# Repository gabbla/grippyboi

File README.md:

# GrippyBoi

Open source and open hardware Haldex gen 1 controller.

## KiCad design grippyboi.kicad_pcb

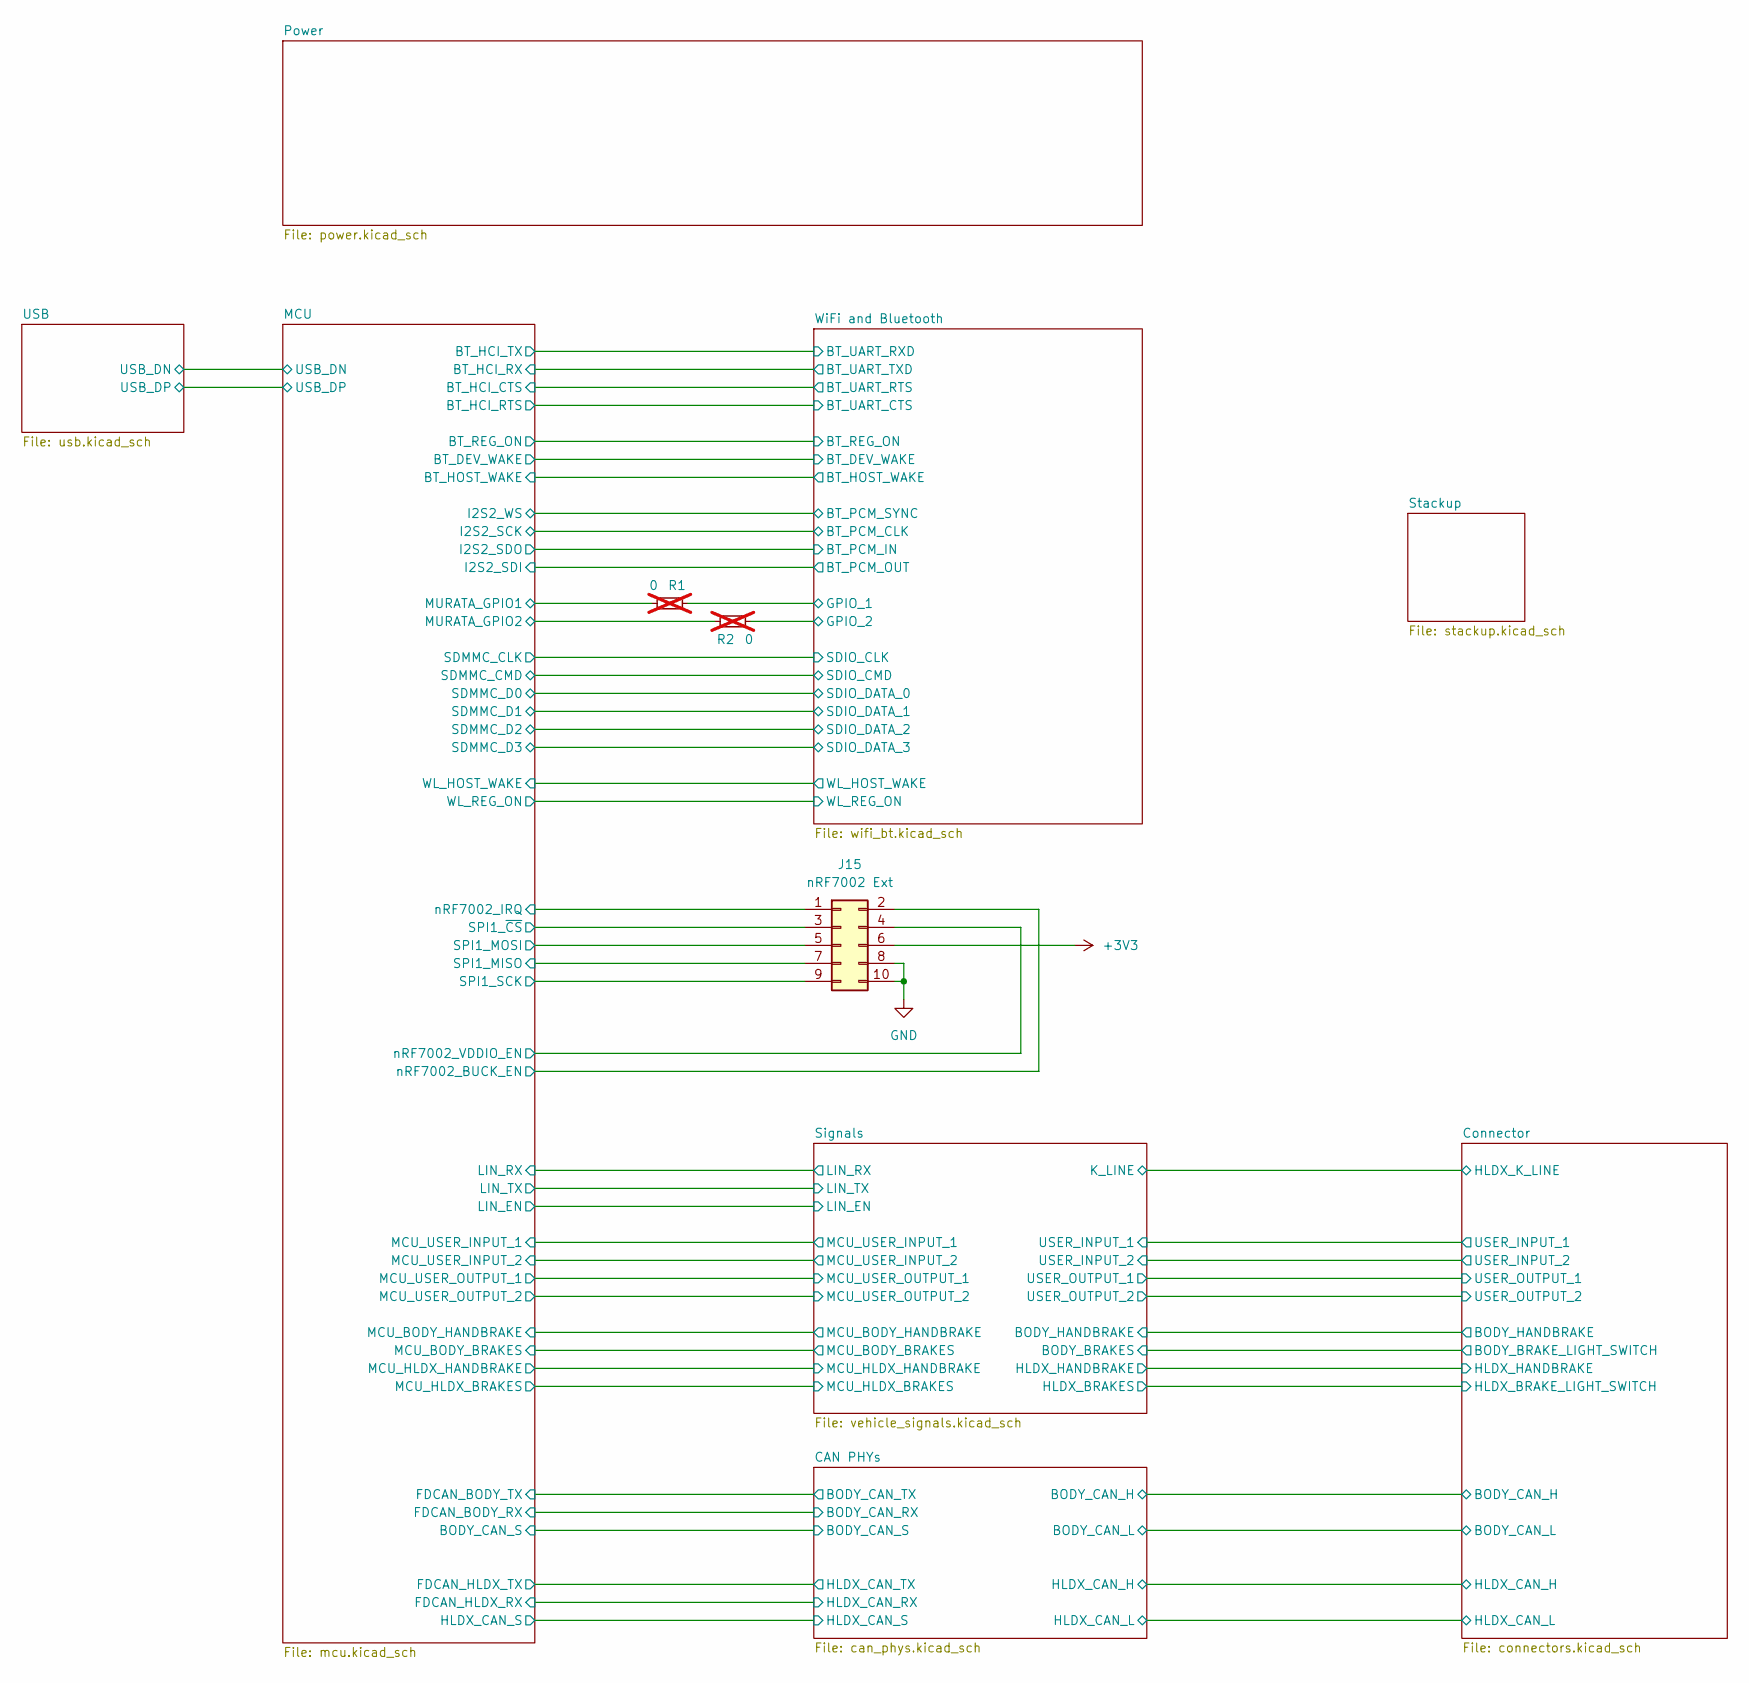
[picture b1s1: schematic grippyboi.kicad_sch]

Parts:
J15: nRF7002 Ext; PinHeader_2x05_P1.27mm_Vertical
R1, R2: 0; R_0603_1608Metric_Pad0.98x0.95mm_HandSolder; not fitted

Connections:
+3V3: J15.6; also elsewhere on the board
/MCU/MURATA_GPIO1: R1.2; also elsewhere on the board
/MCU/MURATA_GPIO2: R2.1; also elsewhere on the board
/MCU/SPI1_MISO: J15.7; also elsewhere on the board
/MCU/SPI1_MOSI: J15.5; also elsewhere on the board
/MCU/SPI1_SCK: J15.9; also elsewhere on the board
/MCU/SPI1_~CS: J15.3; also elsewhere on the board
/MCU/nRF7002_BUCK_EN: J15.2; also elsewhere on the board
/MCU/nRF7002_IRQ: J15.1; also elsewhere on the board
/MCU/nRF7002_VDDIO_EN: J15.4; also elsewhere on the board
/WiFi and Bluetooth/GPIO_1: R1.1; also elsewhere on the board
/WiFi and Bluetooth/GPIO_2: R2.2; also elsewhere on the board
GND: J15.8, J15.10; also elsewhere on the board

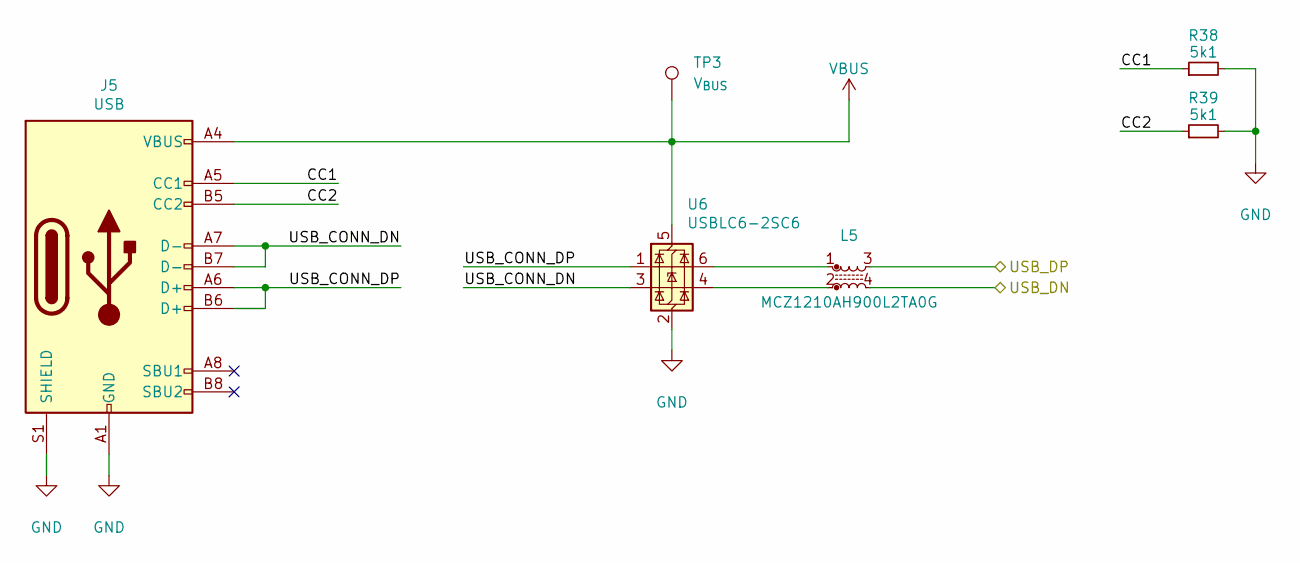
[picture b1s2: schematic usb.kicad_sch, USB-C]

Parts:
J5: USB; USB_C_Receptacle_G-Switch_GT-USB-7010ASV
L5: MCZ1210AH900L2TA0G; MCZ1210AH201L2TA0G
R38, R39: 5k1; R_0603_1608Metric_Pad0.98x0.95mm_HandSolder
TP3: V_{BUS}; TestPoint_Pad_D1.0mm
U6: USBLC6-2SC6; SOT-23-6

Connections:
/MCU/USB_DN: L5.4; also elsewhere on the board
/MCU/USB_DP: L5.3; also elsewhere on the board
/USB/CC1: J5.A5 (CC1), R38.1
/USB/CC2: J5.B5 (CC2), R39.1
/USB/USB_CONN_DN: J5.A7 (D-), J5.B7 (D-), U6.3 (I/O2)
/USB/USB_CONN_DP: J5.A6 (D+), J5.B6 (D+), U6.1 (I/O1)
GND: J5.A1 (GND), J5.A12 (GND), J5.B1 (GND), J5.B12 (GND), J5.S1 (SHIELD), R38.2, R39.2, U6.2 (GND); also elsewhere on the board
unnamed: L5.1, U6.6 (I/O1)
unnamed: L5.2, U6.4 (I/O2)
VBUS: J5.A4 (VBUS), J5.A9 (VBUS), J5.B4 (VBUS), J5.B9 (VBUS), TP3.1, U6.5 (VBUS)

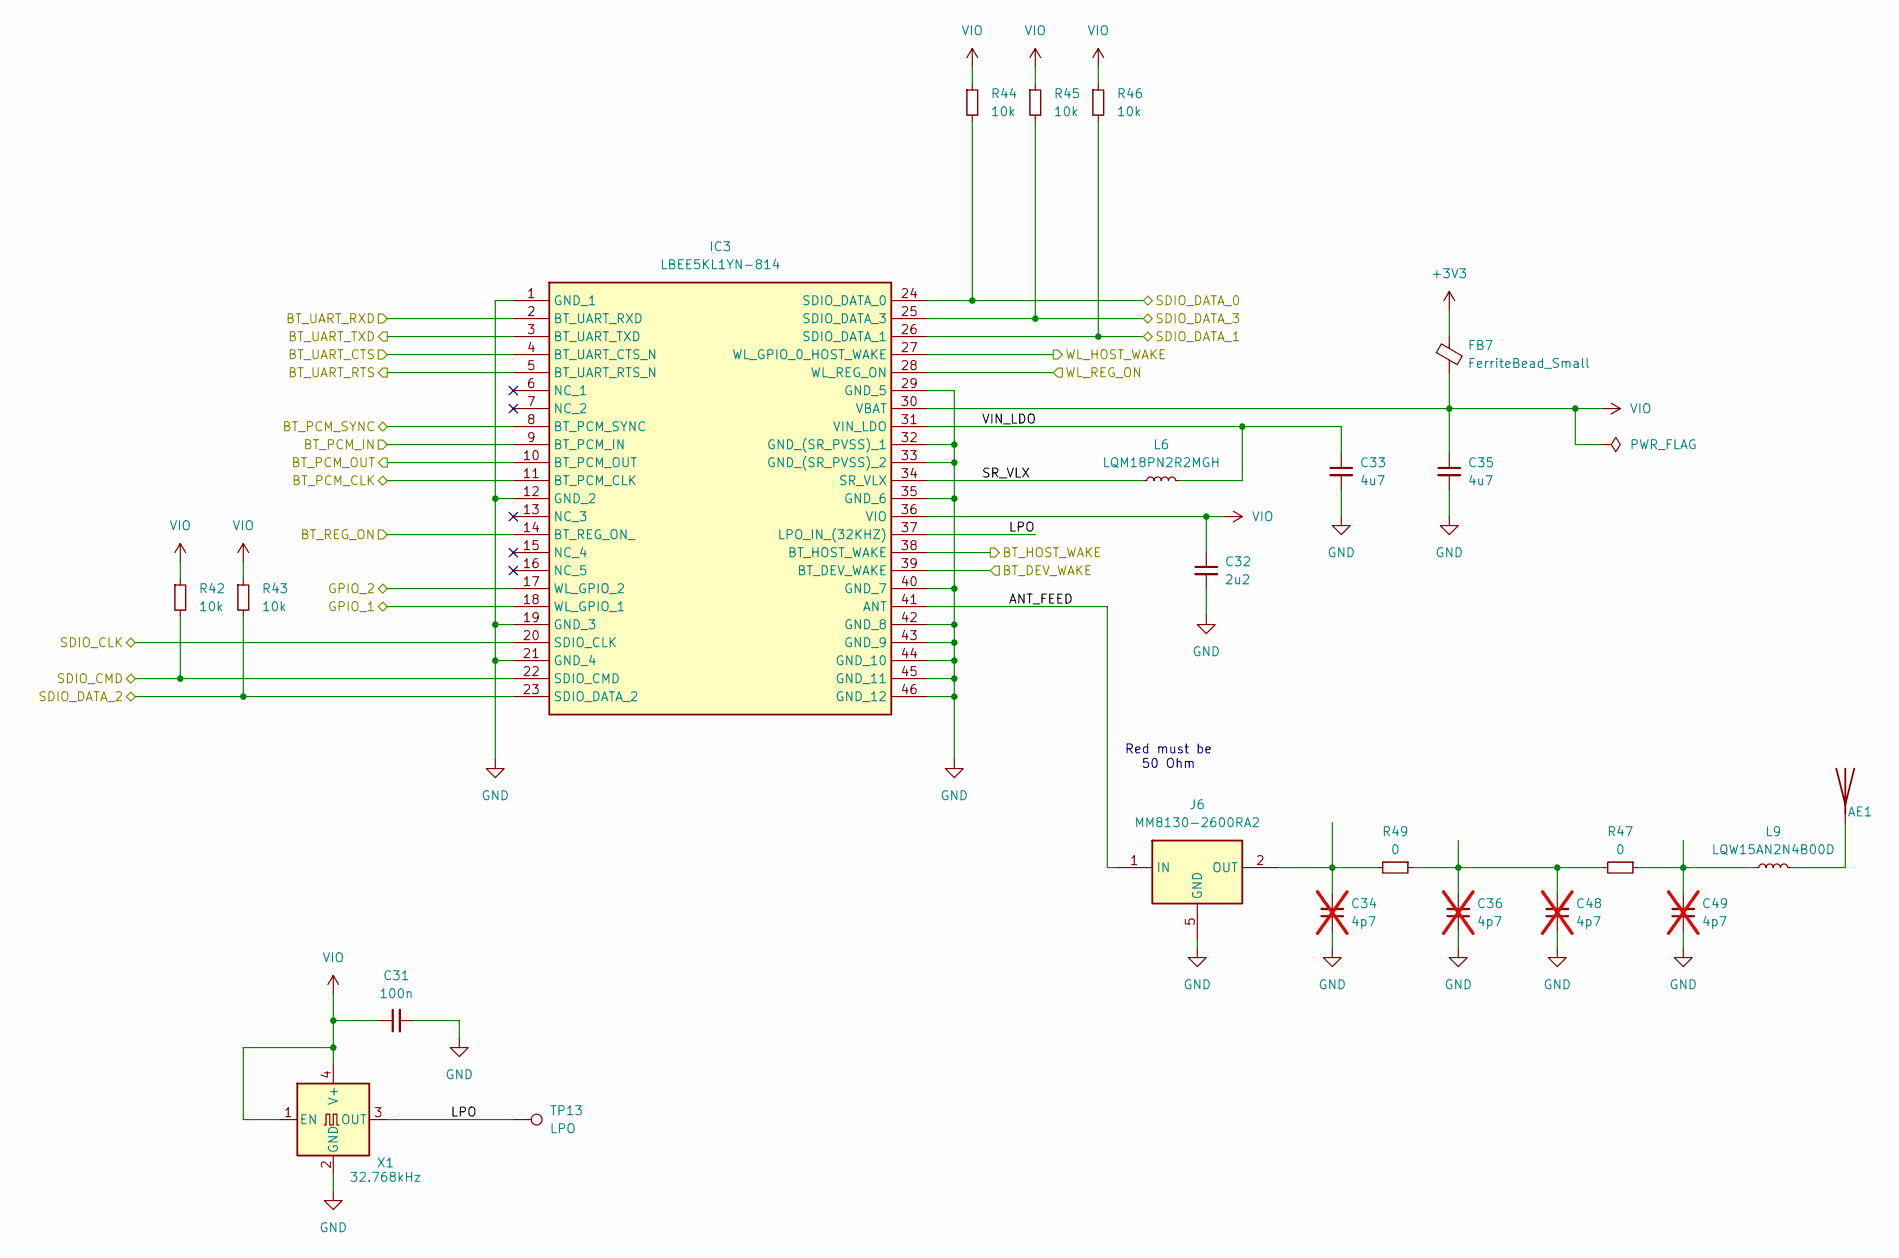
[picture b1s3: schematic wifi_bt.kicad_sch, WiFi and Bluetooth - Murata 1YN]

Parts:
AE1: type1YN-antenna-p2ml4452-1; 1YN_ANTENNA
C31: 100n; C_0603_1608Metric_Pad1.08x0.95mm_HandSolder
C32: 2u2; C_0603_1608Metric_Pad1.08x0.95mm_HandSolder
C33, C35: 4u7; C_0603_1608Metric_Pad1.08x0.95mm_HandSolder
C34, C36, C48, C49: 4p7; C_0402_1005Metric_Pad0.74x0.62mm_HandSolder; not fitted
FB7: FerriteBead_Small; L_0805_2012Metric_Pad1.05x1.20mm_HandSolder
IC3: LBEE5KL1YN-814; LBEE5KL1YN814; Manufacturer_Part_Number LBEE5KL1YN-814; Mouser Part Number 81-LBEE5KL1YN-814
J6: MM8130-2600RA2; MM81302600RA2; Mouser Part Number 81-MM8130-2600RA2
L6: LQM18PN2R2MGH; L_0603_1608Metric_Pad1.05x0.95mm_HandSolder
L9: LQW15AN2N4B00D; L_0402_1005Metric
R42, R43, R44, R45, R46: 10k; R_0402_1005Metric_Pad0.72x0.64mm_HandSolder
R47, R49: 0; R_0402_1005Metric_Pad0.72x0.64mm_HandSolder
TP13: LPO; TestPoint_Pad_D1.0mm
X1: 32.768kHz; Oscillator_SMD_EuroQuartz_XO32-4Pin_3.2x2.5mm

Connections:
+3V3: FB7.1; also elsewhere on the board
/MCU/BT_DEV_WAKE: IC3.39 (BT_DEV_WAKE); also elsewhere on the board
/MCU/BT_HCI_CTS: IC3.5 (BT_UART_RTS_N); also elsewhere on the board
/MCU/BT_HCI_RTS: IC3.4 (BT_UART_CTS_N); also elsewhere on the board
/MCU/BT_HCI_RX: IC3.3 (BT_UART_TXD); also elsewhere on the board
/MCU/BT_HCI_TX: IC3.2 (BT_UART_RXD); also elsewhere on the board
/MCU/BT_HOST_WAKE: IC3.38 (BT_HOST_WAKE); also elsewhere on the board
/MCU/BT_REG_ON: IC3.14 (BT_REG_ON_); also elsewhere on the board
/MCU/I2S2_SCK: IC3.11 (BT_PCM_CLK); also elsewhere on the board
/MCU/I2S2_SDI: IC3.10 (BT_PCM_OUT); also elsewhere on the board
/MCU/I2S2_SDO: IC3.9 (BT_PCM_IN); also elsewhere on the board
/MCU/I2S2_WS: IC3.8 (BT_PCM_SYNC); also elsewhere on the board
/MCU/SDMMC_CLK: IC3.20 (SDIO_CLK); also elsewhere on the board
/MCU/SDMMC_CMD: IC3.22 (SDIO_CMD), R42.2; also elsewhere on the board
/MCU/SDMMC_D0: IC3.24 (SDIO_DATA_0), R44.2; also elsewhere on the board
/MCU/SDMMC_D1: IC3.26 (SDIO_DATA_1), R46.2; also elsewhere on the board
/MCU/SDMMC_D2: IC3.23 (SDIO_DATA_2), R43.2; also elsewhere on the board
/MCU/SDMMC_D3: IC3.25 (SDIO_DATA_3), R45.2; also elsewhere on the board
/MCU/WL_HOST_WAKE: IC3.27 (WL_GPIO_0_HOST_WAKE); also elsewhere on the board
/MCU/WL_REG_ON: IC3.28 (WL_REG_ON); also elsewhere on the board
/WiFi and Bluetooth/ANT_FEED: IC3.41 (ANT), J6.1 (IN)
/WiFi and Bluetooth/GPIO_1: IC3.18 (WL_GPIO_1); also elsewhere on the board
/WiFi and Bluetooth/GPIO_2: IC3.17 (WL_GPIO_2); also elsewhere on the board
/WiFi and Bluetooth/LPO: IC3.37 (LPO_IN_(32KHZ)), TP13.1, X1.3 (OUT)
/WiFi and Bluetooth/SR_VLX: IC3.34 (SR_VLX), L6.1
/WiFi and Bluetooth/VIN_LDO: C33.1, IC3.31 (VIN_LDO), L6.2
GND: C31.2, C32.2, C33.2, C34.1, C35.2, C36.1, C48.1, C49.1, IC3.1 (GND_1), IC3.12 (GND_2), IC3.19 (GND_3), IC3.21 (GND_4), IC3.29 (GND_5), IC3.32 (GND_(SR_PVSS)_1), IC3.33 (GND_(SR_PVSS)_2), IC3.35 (GND_6), IC3.40 (GND_7), IC3.42 (GND_8), IC3.43 (GND_9), IC3.44 (GND_10), IC3.45 (GND_11), IC3.46 (GND_12), J6.3 (GND), J6.4 (GND), J6.5 (GND), J6.6 (GND), X1.2 (GND); also elsewhere on the board
unnamed: AE1.1 (A), L9.2
unnamed: C36.2, C48.2, R47.2, R49.1
unnamed: C49.2, L9.1, R47.1
unnamed: C34.2, J6.2 (OUT), R49.2
VIO: C31.1, C32.1, C35.1, FB7.2, IC3.30 (VBAT), IC3.36 (VIO), R42.1, R43.1, R44.1, R45.1, R46.1, X1.1 (EN), X1.4 (V+)

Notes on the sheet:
Red must be 50 Ohm

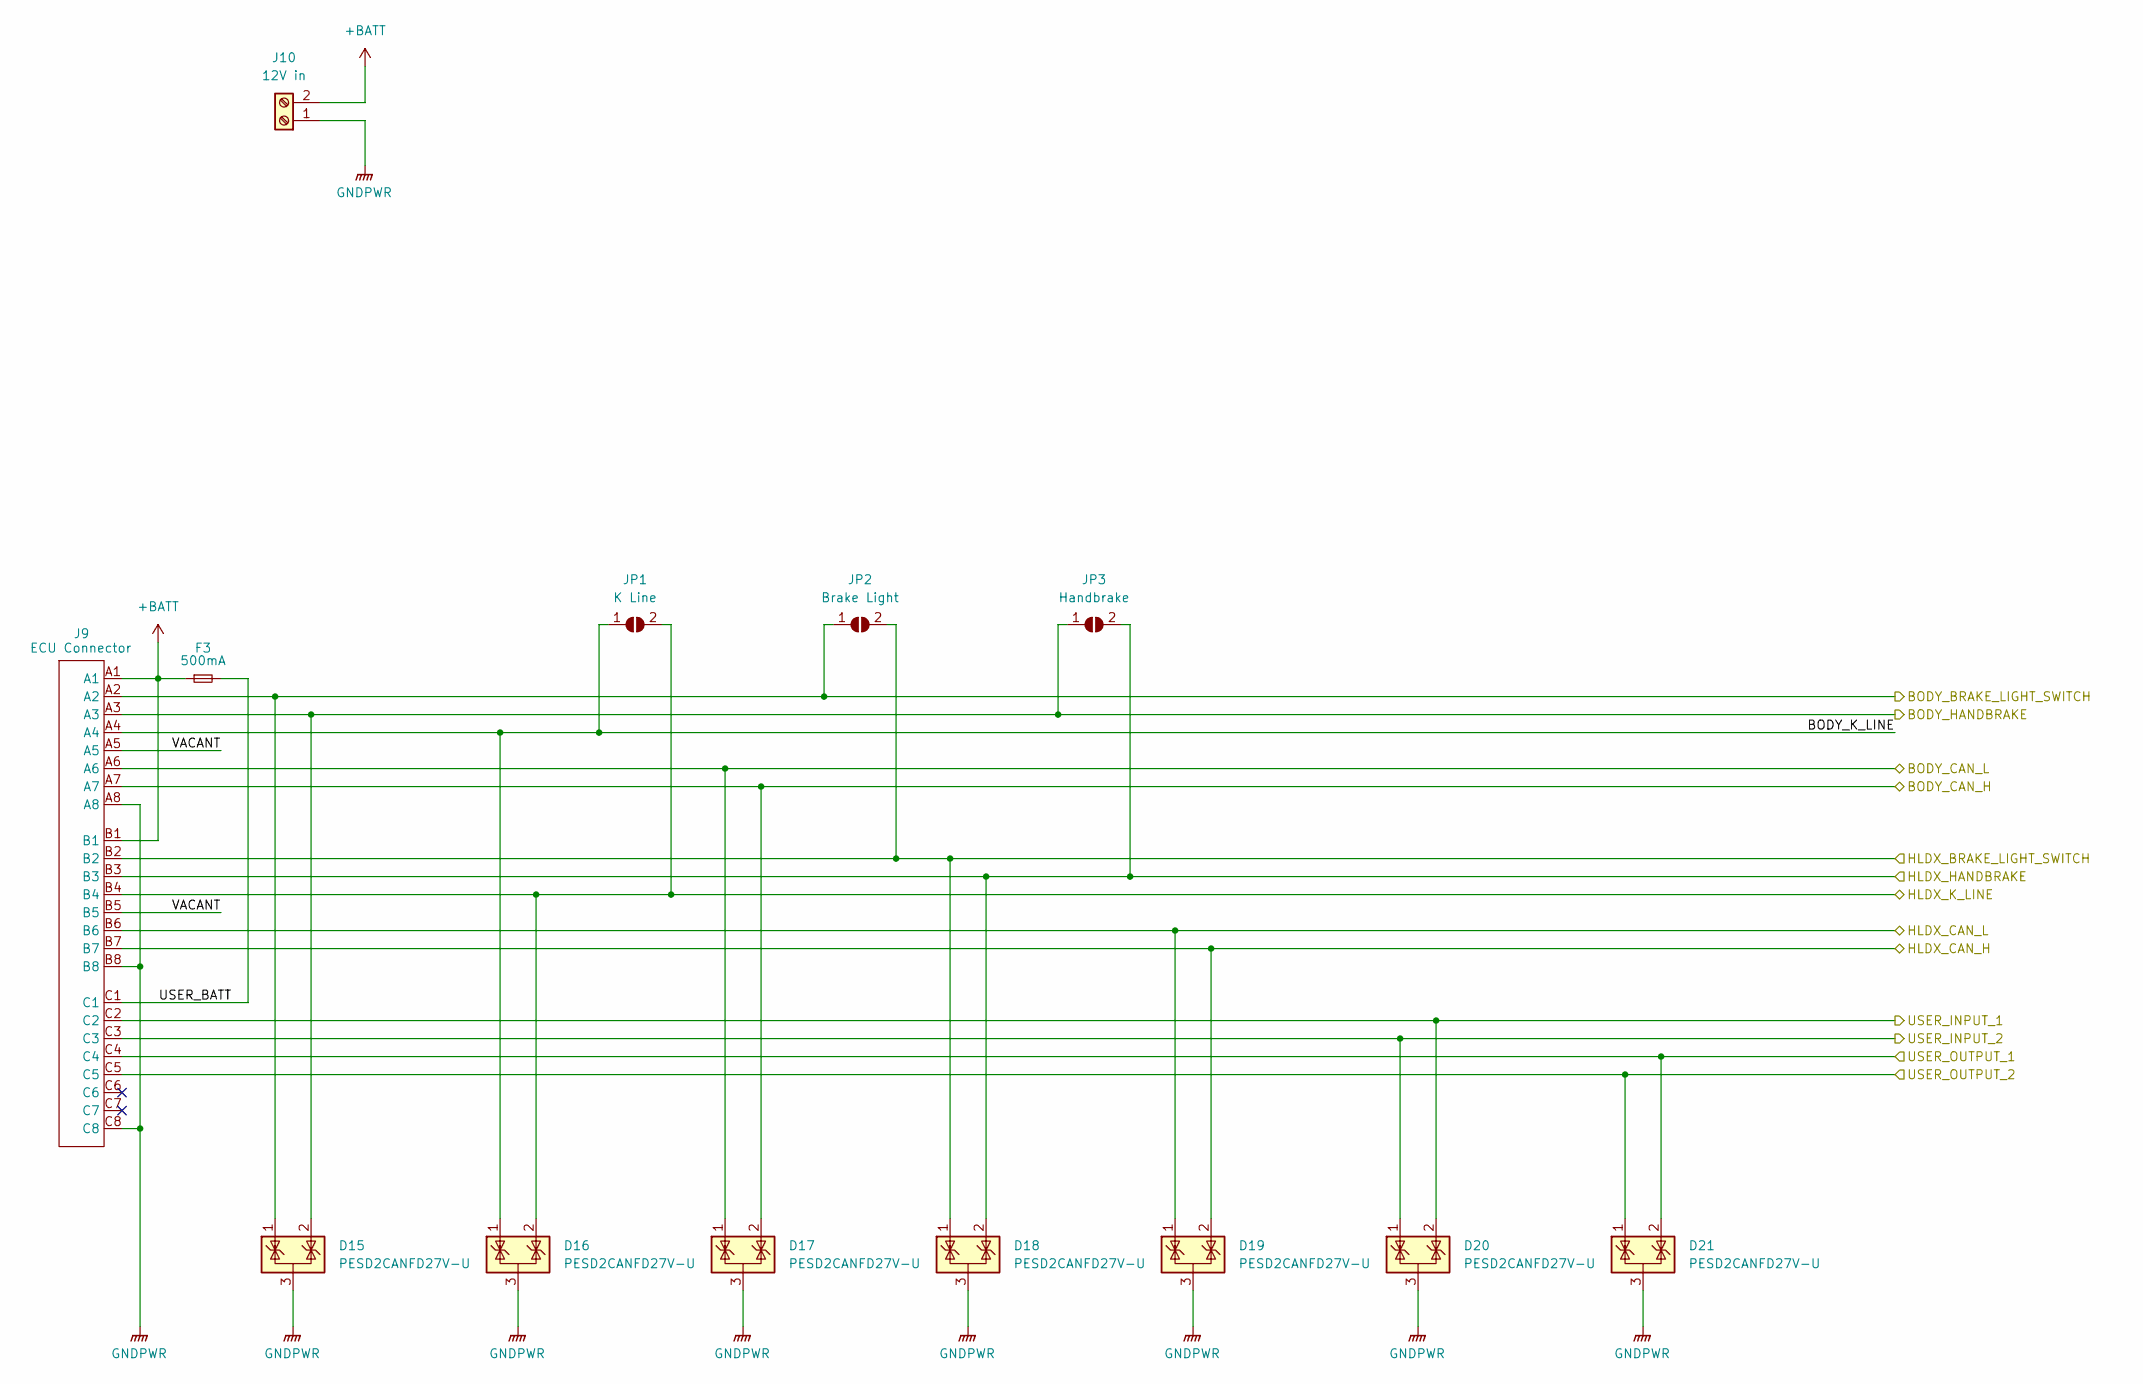
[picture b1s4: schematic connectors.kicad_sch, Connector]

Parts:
D15, D16, D17, D18, D19, D20, D21: PESD2CANFD27V-U; SOT-23
F3: 500mA; Fuse_1206_3216Metric
J9: ECU Connector; ecu24
J10: 12V in; TerminalBlock_Phoenix_PT-1,5-2-3.5-H_1x02_P3.50mm_Horizontal
JP1: K Line; SolderJumper-2_P1.3mm_Open_TrianglePad1.0x1.5mm
JP2: Brake Light; SolderJumper-2_P1.3mm_Open_TrianglePad1.0x1.5mm
JP3: Handbrake; SolderJumper-2_P1.3mm_Open_TrianglePad1.0x1.5mm

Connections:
+BATT: F3.1, J9.A1, J9.B1, J10.2; also elsewhere on the board
/CAN PHYs/BODY_CAN_H: D17.2 (K), J9.A7; also elsewhere on the board
/CAN PHYs/BODY_CAN_L: D17.1 (K), J9.A6; also elsewhere on the board
/CAN PHYs/HLDX_CAN_H: D19.2 (K), J9.B7; also elsewhere on the board
/CAN PHYs/HLDX_CAN_L: D19.1 (K), J9.B6; also elsewhere on the board
/Connector/BODY_BRAKE_LIGHT_SWITCH: D15.1 (K), J9.A2, JP2.1 (A); also elsewhere on the board
/Connector/BODY_HANDBRAKE: D15.2 (K), J9.A3, JP3.1 (A); also elsewhere on the board
/Connector/BODY_K_LINE: D16.1 (K), J9.A4, JP1.1 (A)
/Connector/HLDX_BRAKE_LIGHT_SWITCH: D18.1 (K), J9.B2, JP2.2 (B); also elsewhere on the board
/Connector/HLDX_HANDBRAKE: D18.2 (K), J9.B3, JP3.2 (B); also elsewhere on the board
/Connector/HLDX_K_LINE: D16.2 (K), J9.B4, JP1.2 (B); also elsewhere on the board
/Connector/USER_BATT: F3.2, J9.C1
/Connector/USER_INPUT_1: D20.2 (K), J9.C2; also elsewhere on the board
/Connector/USER_INPUT_2: D20.1 (K), J9.C3; also elsewhere on the board
/Connector/USER_OUTPUT_1: D21.2 (K), J9.C4; also elsewhere on the board
/Connector/USER_OUTPUT_2: D21.1 (K), J9.C5; also elsewhere on the board
/Connector/VACANT: J9.A5, J9.B5
GNDPWR: D15.3 (A), D16.3 (A), D17.3 (A), D18.3 (A), D19.3 (A), D20.3 (A), D21.3 (A), J9.A8, J9.B8, J9.C8, J10.1; also elsewhere on the board

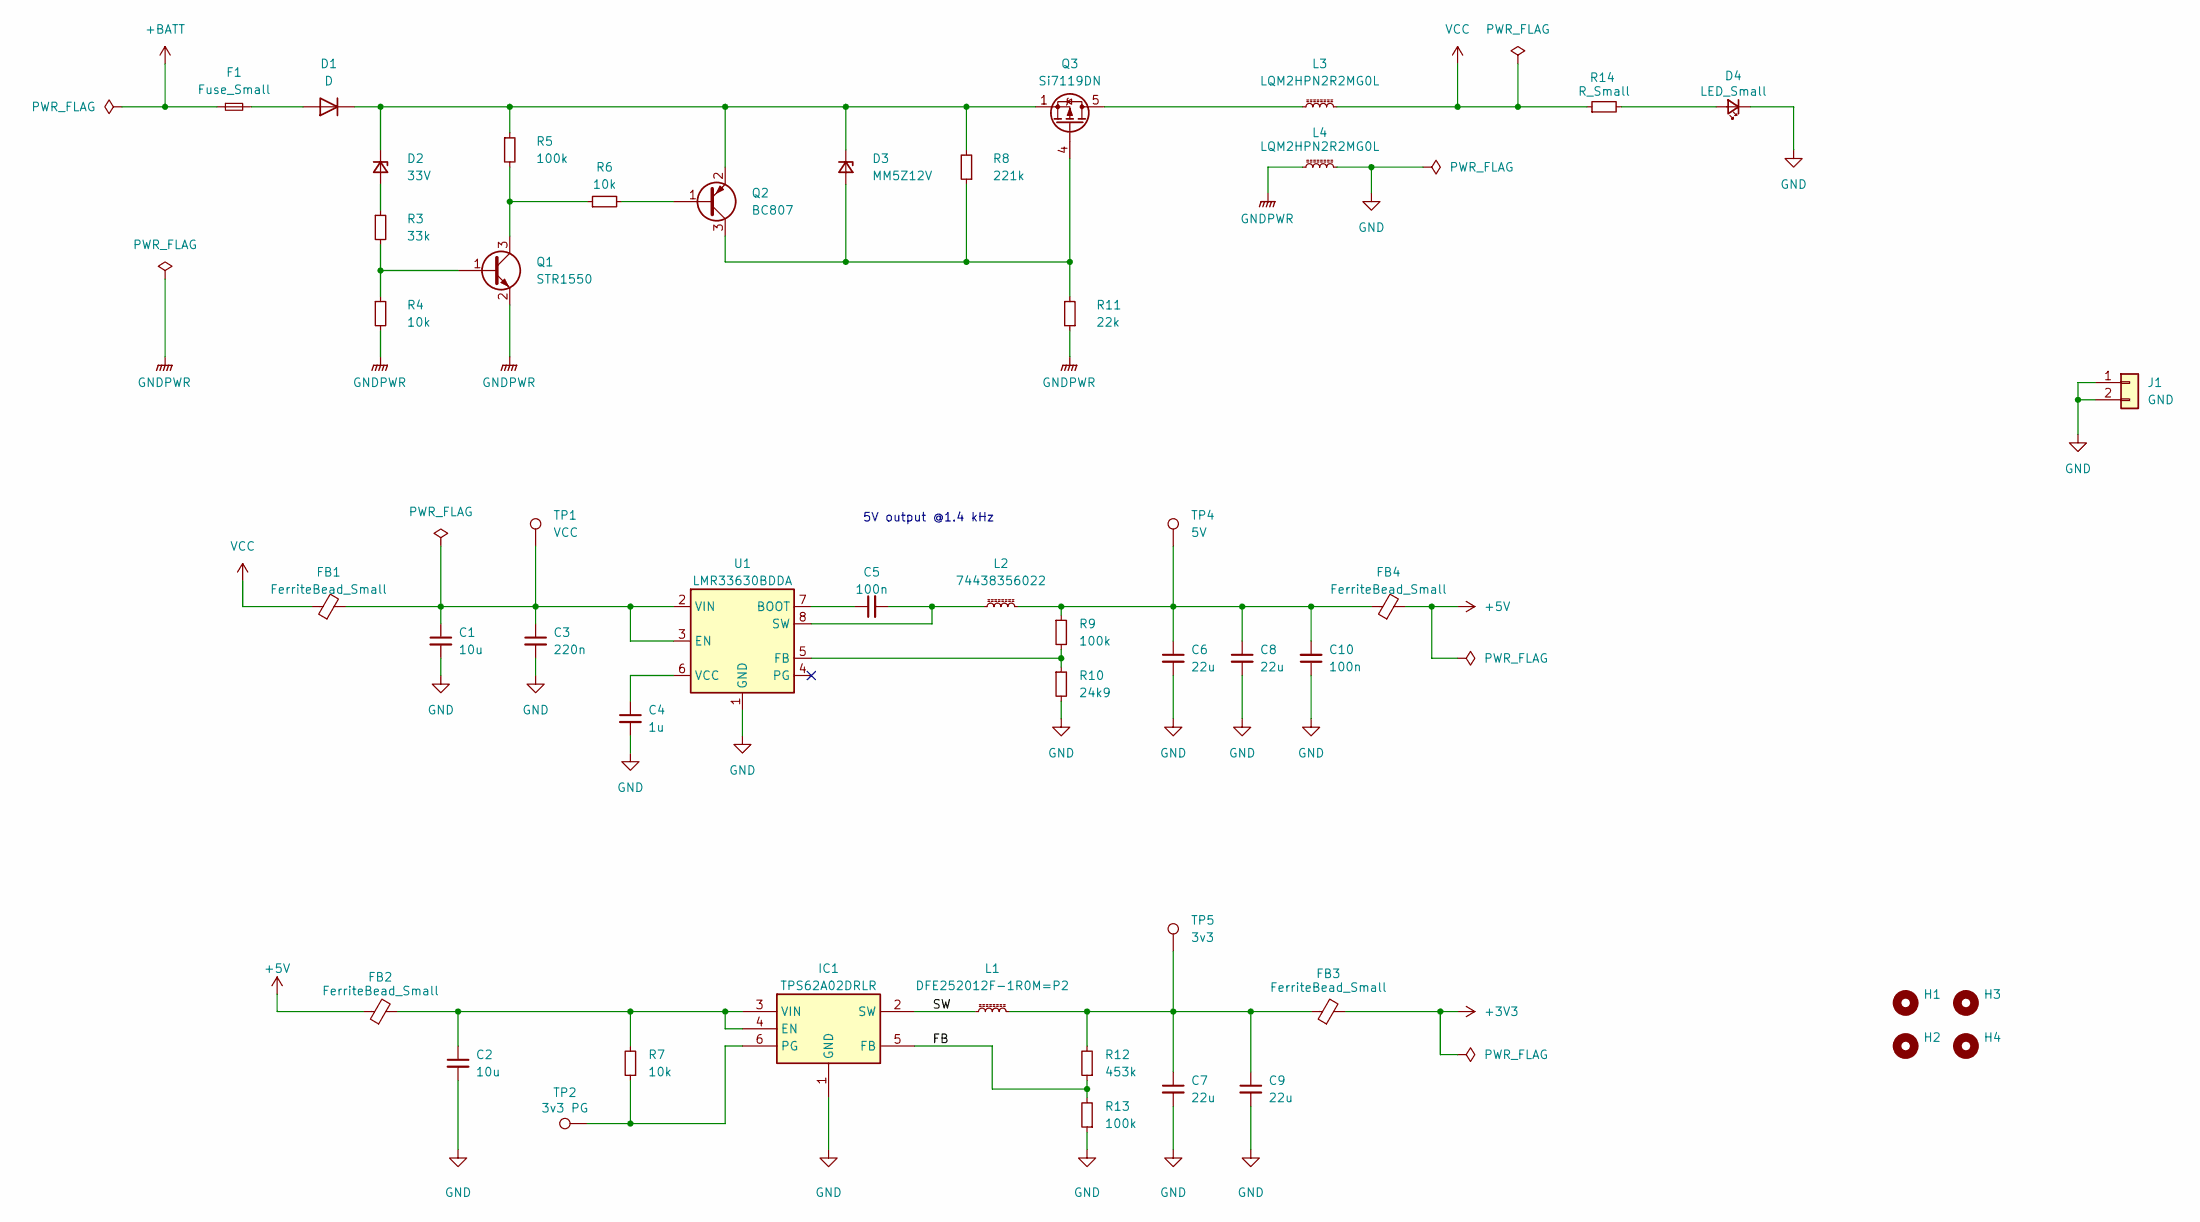
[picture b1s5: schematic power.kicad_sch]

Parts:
C1, C2: 10u; C_0805_2012Metric_Pad1.18x1.45mm_HandSolder
C3: 220n; C_0603_1608Metric_Pad1.08x0.95mm_HandSolder
C4: 1u; C_0603_1608Metric_Pad1.08x0.95mm_HandSolder
C5, C10: 100n; C_0603_1608Metric_Pad1.08x0.95mm_HandSolder
C6, C7, C8, C9: 22u; C_0805_2012Metric_Pad1.18x1.45mm_HandSolder
D1: D; D_SMB_Handsoldering
D2: 33V; D_SOD-123
D3: MM5Z12V; D_SOD-523
D4: LED_Small; LED_0603_1608Metric_Pad1.05x0.95mm_HandSolder
F1: Fuse_Small; Fuse_1206_3216Metric
FB1, FB2, FB3, FB4: FerriteBead_Small; L_0805_2012Metric_Pad1.05x1.20mm_HandSolder
H1, H2, H3, H4: MountingHole; MountingHole_3.2mm_M3
IC1: TPS62A02DRLR; SOTFL50P160X60-6N; Manufacturer_Part_Number TPS62A02DRLR; Mouser Part Number 595-TPS62A02DRLR
J1: GND; PinHeader_1x02_P2.54mm_Vertical
L1: DFE252012F-1R0M=P2; L_1008_2520Metric_Pad1.43x2.20mm_HandSolder
L2: 74438356022; L_Wuerth_MAPI-4020
L3, L4: LQM2HPN2R2MG0L; L_1008_2520Metric_Pad1.43x2.20mm_HandSolder
Q1: STR1550; TSOT-23
Q2: BC807; SOT-23
Q3: Si7119DN; Vishay_PowerPAK_1212-8_Single
R3: 33k; R_0603_1608Metric_Pad0.98x0.95mm_HandSolder
R4, R6, R7: 10k; R_0603_1608Metric_Pad0.98x0.95mm_HandSolder
R5, R9, R13: 100k; R_0603_1608Metric_Pad0.98x0.95mm_HandSolder
R8: 221k; R_0603_1608Metric_Pad0.98x0.95mm_HandSolder
R10: 24k9; R_0603_1608Metric_Pad0.98x0.95mm_HandSolder
R11: 22k; R_0603_1608Metric_Pad0.98x0.95mm_HandSolder
R12: 453k; R_0603_1608Metric_Pad0.98x0.95mm_HandSolder
R14: R_Small; R_0603_1608Metric_Pad0.98x0.95mm_HandSolder
TP1: VCC; TestPoint_Pad_D1.5mm
TP2: 3v3 PG; TestPoint_Pad_D1.0mm
TP4: 5V; TestPoint_Pad_D1.5mm
TP5: 3v3; TestPoint_Pad_D1.5mm
U1: LMR33630BDDA; Texas_HSOP-8-1EP_3.9x4.9mm_P1.27mm_ThermalVias

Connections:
+3V3: FB3.2; also elsewhere on the board
+5V: FB2.1, FB4.2; also elsewhere on the board
+BATT: F1.1; also elsewhere on the board
/Power/FB: IC1.5 (FB), R12.1, R13.2
/Power/SW: IC1.2 (SW), L1.1
GND: C1.2, C2.2, C3.2, C4.2, C6.2, C7.2, C8.2, C9.2, C10.1, D4.1 (K), IC1.1 (GND), J1.1, J1.2, L4.2, R10.2, R13.1, U1.1 (GND), U1.9 (GND); also elsewhere on the board
GNDPWR: L4.1, Q1.2 (E), R4.2, R11.1; also elsewhere on the board
unnamed: C7.1, C9.1, FB3.1, L1.2, R12.2, TP5.1
unnamed: C6.1, C8.1, C10.2, FB4.1, L2.2, R9.1, TP4.1
unnamed: D1.2 (A), F1.2
unnamed: D1.1 (K), D2.1 (K), D3.1 (K), Q2.2 (E), Q3.1 (S), Q3.2 (S), Q3.3 (S), R5.1, R8.2
unnamed: D2.2 (A), R3.1
unnamed: D3.2 (A), Q2.3 (C), Q3.4 (G), R8.1, R11.2
unnamed: D4.2 (A), R14.2
unnamed: C2.1, FB2.2, IC1.3 (VIN), IC1.4 (EN), R7.2
unnamed: IC1.6 (PG), R7.1, TP2.1
unnamed: Q1.1 (B), R3.2, R4.1
unnamed: Q1.3 (C), R5.2, R6.1
unnamed: Q2.1 (B), R6.2
unnamed: L3.1, Q3.5 (D)
unnamed: C5.1, U1.7 (BOOT)
unnamed: C1.1, C3.1, FB1.2, TP1.1, U1.2 (VIN), U1.3 (EN)
unnamed: R9.2, R10.1, U1.5 (FB)
unnamed: C5.2, L2.1, U1.8 (SW)
unnamed: C4.1, U1.6 (VCC)
VCC: FB1.1, L3.2, R14.1; also elsewhere on the board

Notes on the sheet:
5V output @1.4 kHz

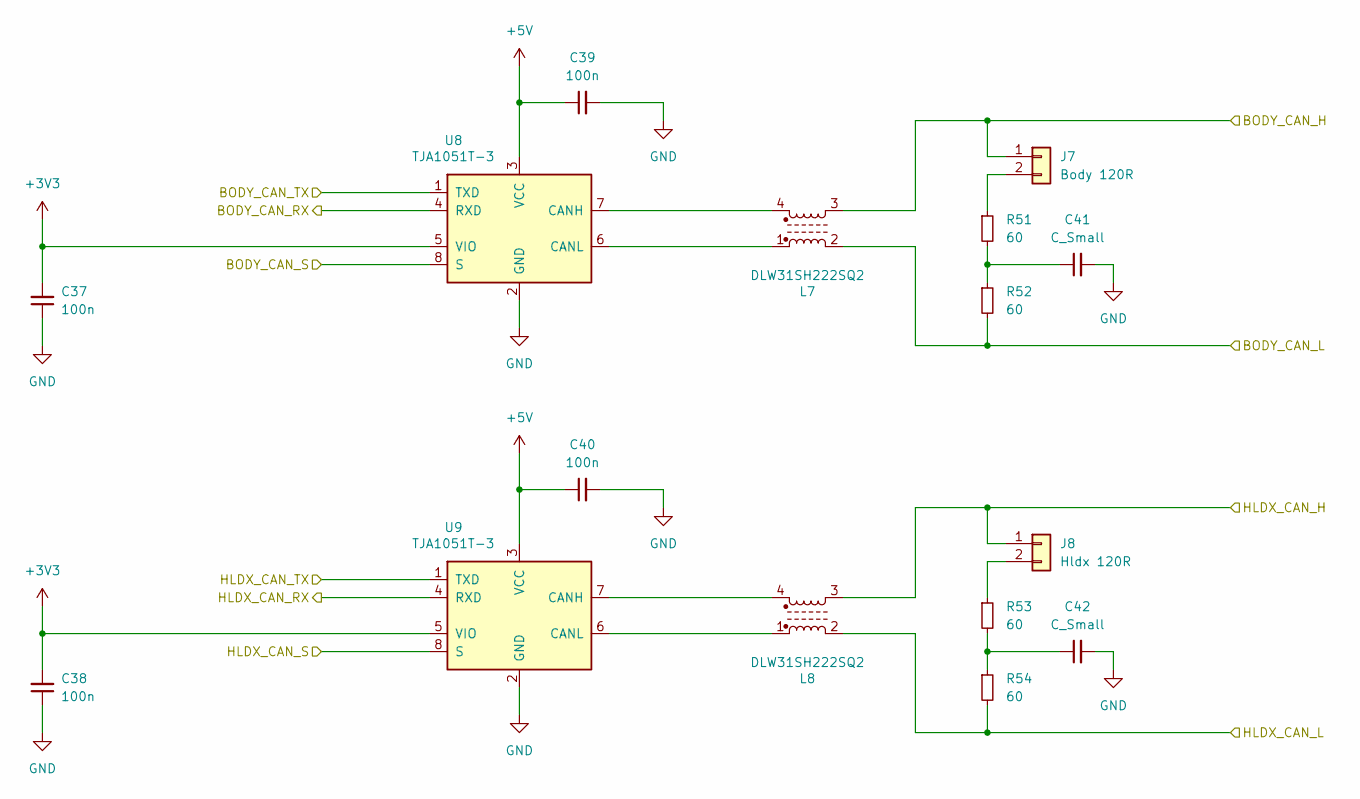
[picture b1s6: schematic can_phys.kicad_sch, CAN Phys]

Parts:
C37, C38, C39, C40: 100n; C_0603_1608Metric_Pad1.08x0.95mm_HandSolder
C41, C42: C_Small; C_0603_1608Metric_Pad1.08x0.95mm_HandSolder
J7: Body 120R; PinHeader_1x02_P2.54mm_Vertical
J8: Hldx 120R; PinHeader_1x02_P2.54mm_Vertical
L7, L8: DLW31SH222SQ2; DLW31SH222SQ2L
R51, R52, R53, R54: 60; R_0603_1608Metric_Pad0.98x0.95mm_HandSolder
U8, U9: TJA1051T-3; SOIC-8_3.9x4.9mm_P1.27mm

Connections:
+3V3: C37.2, C38.2, U8.5 (VIO), U9.5 (VIO); also elsewhere on the board
+5V: C39.1, C40.1, U8.3 (VCC), U9.3 (VCC); also elsewhere on the board
/CAN PHYs/BODY_CAN_H: J7.1, L7.3; also elsewhere on the board
/CAN PHYs/BODY_CAN_L: L7.2, R52.2; also elsewhere on the board
/CAN PHYs/BODY_CAN_RX: U8.4 (RXD); also elsewhere on the board
/CAN PHYs/BODY_CAN_S: U8.8 (S); also elsewhere on the board
/CAN PHYs/BODY_CAN_TX: U8.1 (TXD); also elsewhere on the board
/CAN PHYs/HLDX_CAN_H: J8.1, L8.3; also elsewhere on the board
/CAN PHYs/HLDX_CAN_L: L8.2, R54.2; also elsewhere on the board
/CAN PHYs/HLDX_CAN_RX: U9.4 (RXD); also elsewhere on the board
/CAN PHYs/HLDX_CAN_S: U9.8 (S); also elsewhere on the board
/CAN PHYs/HLDX_CAN_TX: U9.1 (TXD); also elsewhere on the board
GND: C37.1, C38.1, C39.2, C40.2, C41.2, C42.2, U8.2 (GND), U9.2 (GND); also elsewhere on the board
unnamed: C41.1, R51.2, R52.1
unnamed: C42.1, R53.2, R54.1
unnamed: J7.2, R51.1
unnamed: J8.2, R53.1
unnamed: L7.4, U8.7 (CANH)
unnamed: L7.1, U8.6 (CANL)
unnamed: L8.4, U9.7 (CANH)
unnamed: L8.1, U9.6 (CANL)
